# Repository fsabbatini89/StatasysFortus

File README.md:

# StatasysFortus
This is a man-in-the-middle technique for Statasys Fortus machine

Basically you put a real cartdrige on each bay with full filament on it.
The PCB of the bay is connected to this project board input and output is connected to the original
fortus cable.
This PCB captures the "WRITE ON CARTDRIGE" commands from the main cpu to the bay pcb and replies accordingly
but that message never gets to the bay pcb so the chip is never ever written so after a machine reset, cartdrige is
full again.

Cartridge cache file of machine as to be erased so the serial number of cartrige is forggoten at startup so machine thinks
new full filament is set.

Happy printing!

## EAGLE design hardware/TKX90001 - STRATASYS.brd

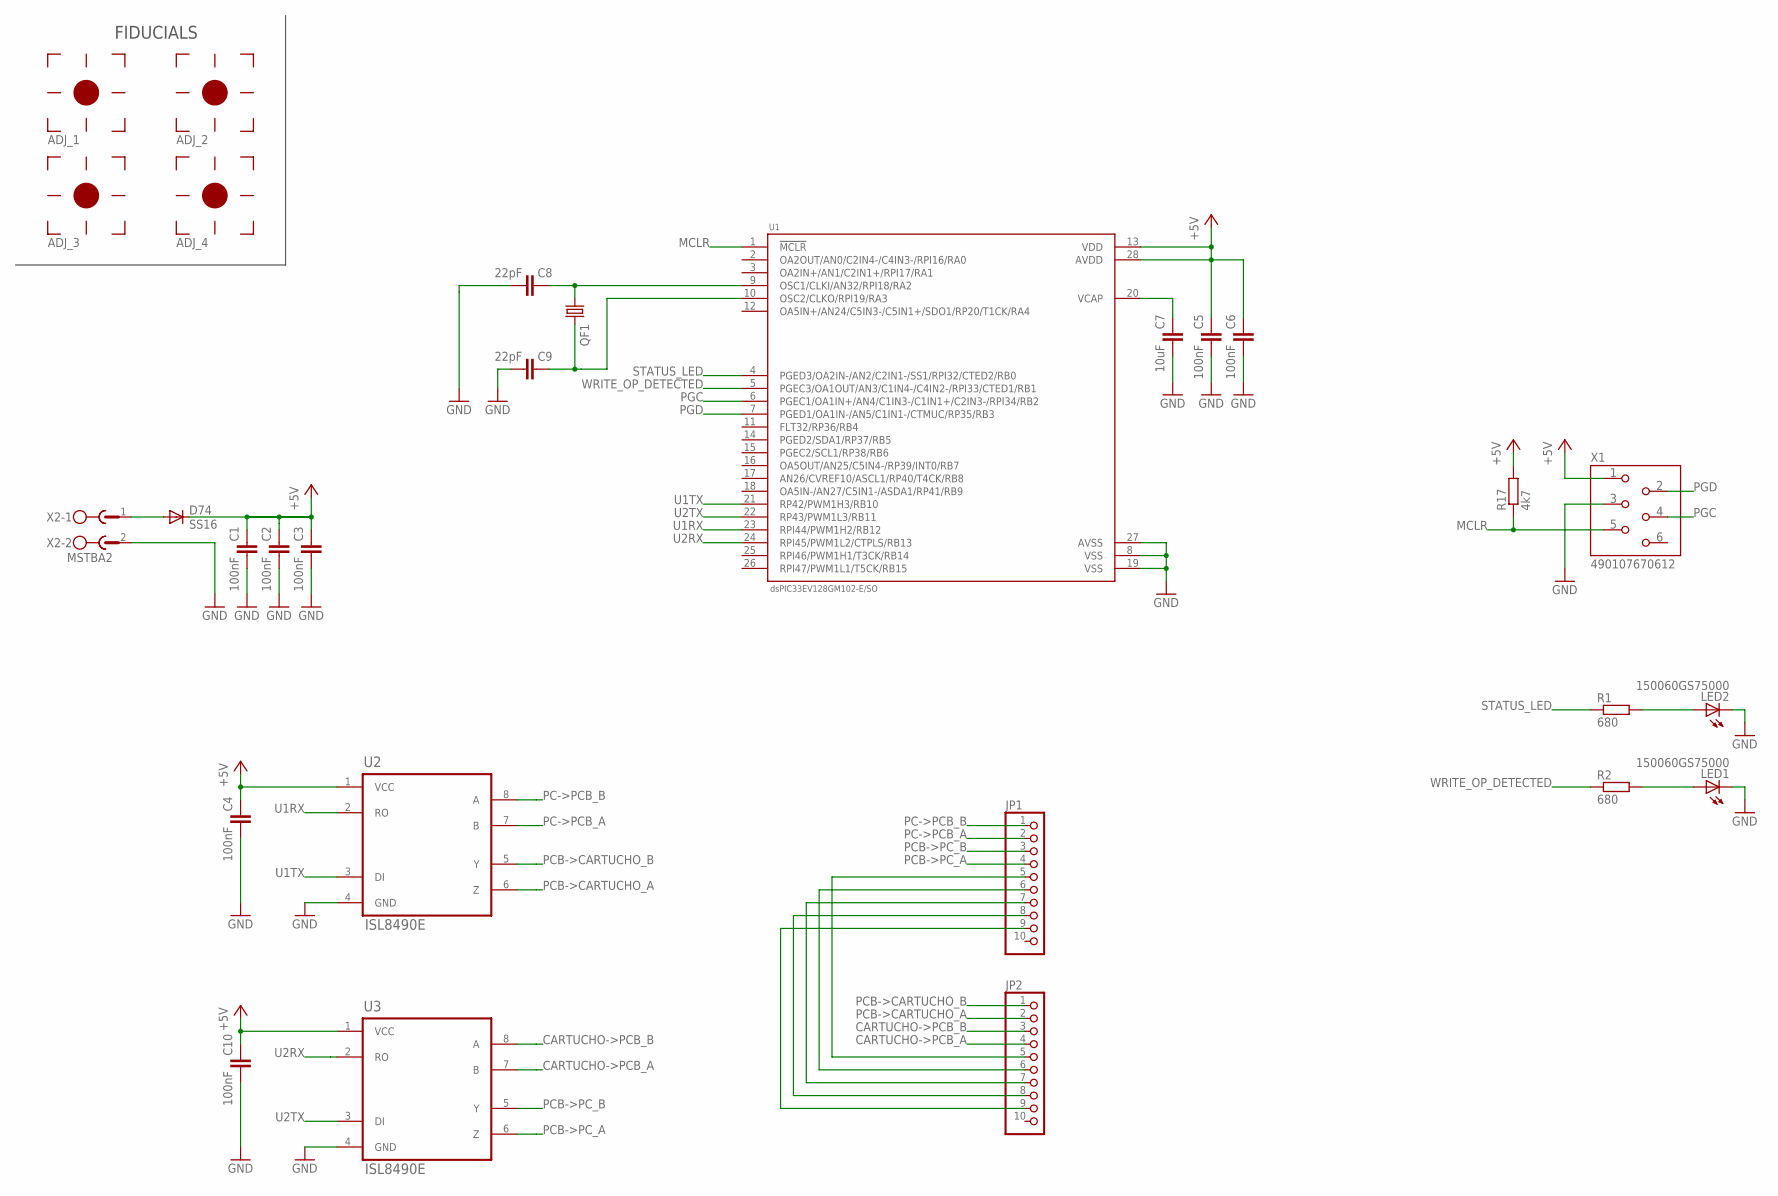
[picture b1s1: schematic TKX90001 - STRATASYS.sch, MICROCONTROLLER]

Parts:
ADJ_1, ADJ_2, ADJ_3, ADJ_4: FIDUCIAL
C1, C2, C3, C4, C5, C6, C10: 100nF; C0603K; PARTNO 885012206020
C7: 10uF; C1206K; PARTNO TAJA106K016RNJV
C8, C9: 22pF; C0603K; PARTNO C0603C220M4RACAUTO
D74: SS16; SMB; PARTNO SS16T3G
JP1, JP2: PINHD-1X10/90; 1X10/90
LED1, LED2: 150060GS75000; SML0603; PARTNO 150060GS75000
QF1: CRYSTALHC49S; HC49/S
R1, R2: 680; R0603; PARTNO RC0603FR-13680RL
R17: 4k7; R0603; PARTNO RC0603FR-074K7L
U1: dsPIC33EV128GM102-E/SO; SOIC127P1028X256-28N; PARTNO dsPIC33EV128GM102-E/SO
U2, U3: ISL8490E; SOIC127P600X175-8N; PARTNO ISL8490EIBZ
X1: 490107670612; REDFIT_6POS
X2: MSTBA2

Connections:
+5V: C1.1, C2.1, C3.1, C4.1, C5.1, C6.1, C10.1, D74.C, R17.2, U1.13 (VDD), U1.28 (AVDD), U2.1 (VCC), U3.1 (VCC), X1.P$1
CARTUCHO->PCB_A: JP2.4, U3.7 (B)
CARTUCHO->PCB_B: JP2.3, U3.8 (A)
GND: C1.2, C2.2, C3.2, C4.2, C5.2, C6.2, C7.2, C8.2, C9.2, C10.2, LED1.C, LED2.C, U1.8 (VSS), U1.19 (VSS), U1.27 (AVSS), U2.4 (GND), U3.4 (GND), X1.P$3, X2.2
MCLR: R17.1, U1.1 (!MCLR), X1.P$5
unnamed: LED1.A, R2.2
unnamed: D74.A, X2.1
unnamed: C7.1, U1.20 (VCAP)
unnamed: C8.1, QF1.1, U1.9 (OSC1/CLKI/AN32/RPI18/RA2)
unnamed: LED2.A, R1.2
unnamed: C9.1, QF1.2, U1.10 (OSC2/CLKO/RPI19/RA3)
unnamed: JP1.5, JP2.5
unnamed: JP1.6, JP2.6
unnamed: JP1.7, JP2.7
unnamed: JP1.8, JP2.8
unnamed: JP1.9, JP2.9
PC->PCB_A: JP1.2, U2.7 (B)
PC->PCB_B: JP1.1, U2.8 (A)
PCB->CARTUCHO_A: JP2.2, U2.6 (Z)
PCB->CARTUCHO_B: JP2.1, U2.5 (Y)
PCB->PC_A: JP1.4, U3.6 (Z)
PCB->PC_B: JP1.3, U3.5 (Y)
PGC: U1.6 (PGEC1/OA1IN+/AN4/C1IN3-/C1IN1+/C2IN3-/R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), X1.P$4
PGD: U1.7 (PGED1/OA1IN-/AN5/C1IN1-/CTMUC/RP35/RB3), X1.P$2
STATUS_LED: R1.1, U1.4 (PGED3/OA2IN-/AN2/C2IN1-/SS1/RPI32/CTED2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)
U1RX: U1.23 (RPI44/PWM1H2/RB12), U2.2 (RO)
U1TX: U1.21 (RP42/PWM1H3/RB10), U2.3 (DI)
U2RX: U1.24 (RPI45/PWM1L2/CTPLS/RB13), U3.2 (RO)
U2TX: U1.22 (RP43/PWM1L3/RB11), U3.3 (DI)
WRITE_OP_DETECTED: R2.1, U1.5 (PGEC3/OA1OUT/AN3/C1IN4-/C4IN2-/RPI33/CT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)

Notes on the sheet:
FIDUCIALS

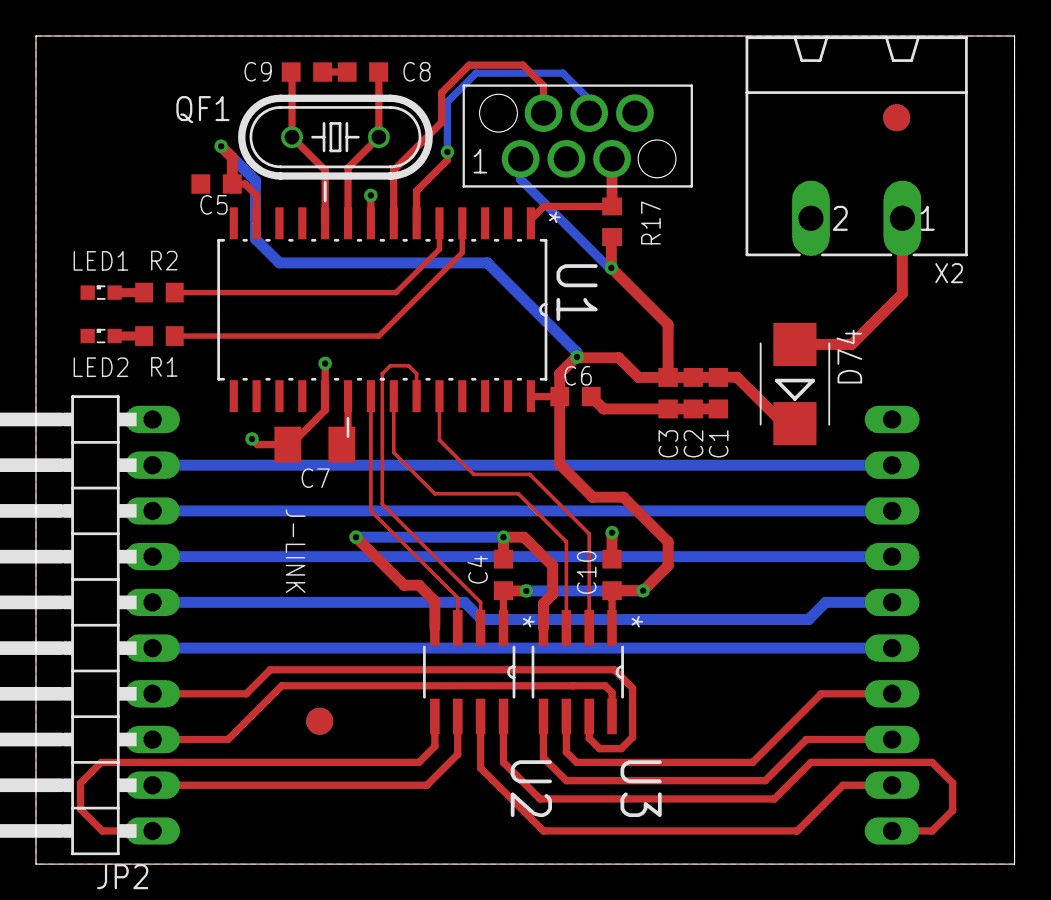
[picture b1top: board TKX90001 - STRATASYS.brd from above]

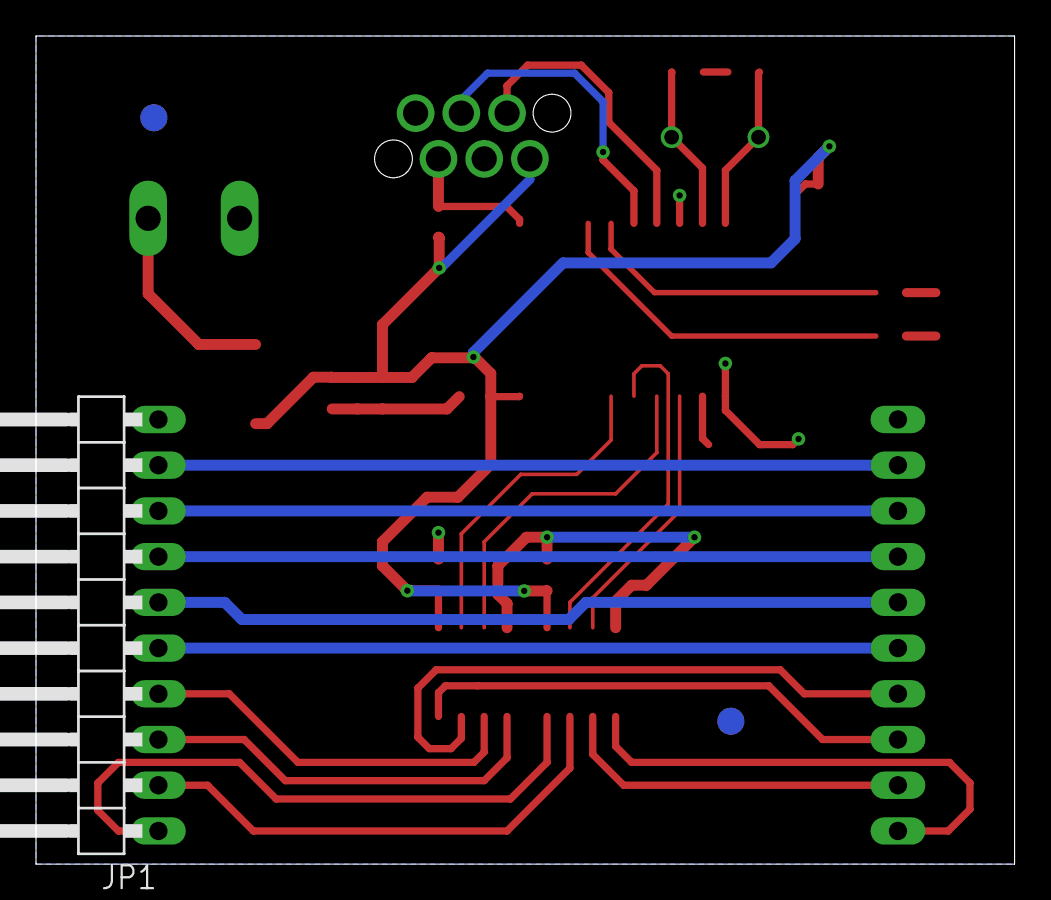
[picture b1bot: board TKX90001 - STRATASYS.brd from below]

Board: 2 copper layers, 54.4 x 46.0 mm, 28 parts (3 on the bottom side), 30 nets.

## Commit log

2025-01-13 Working commit of project
